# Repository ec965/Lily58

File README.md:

# SMD Lily58
* ATMEGA32U4 and STM32F072 variants
* Full SMD MCU and components.
* Original parts kept true to original placement where ever possible.
* Reversible PCB to reduce costs.
* USB C port on the left side.
* MCP23017 IO expander to reduce cost over two MCUs.

# Lily58
Lily58 is 6*4+4keys column-staggered split keyboard.

## [Document Site Here](https://kata0510.github.io/Lily58-Document/)

# Type

- Lily58 Pro
  - [PCB Data](https://github.com/kata0510/Lily58/tree/master/Pro/PCB)
  - [BuildGuide JP](https://kata0510.github.io/Lily58-Document/Lily58_Pro.html)
  - [BuildGuide EN](https://kata0510.github.io/Lily58-Document/Lily58_Pro_BG_ENG.html)
  - [Shop(Yushakobo)](https://yushakobo.jp/shop/lily58-pro/)
- Lily58 Lite Rev2
  - [BuildGuide(YouTube)](https://www.youtube.com/watch?v=t6HLQvqlsVM)
  - [BuildInfo](https://kata0510.github.io/Lily58-Document/Lily58_Lite_Rev2.html)
  - [Shop(BOOTH)](https://booth.pm/ja/items/1963895)
  - [Shop(Yushakobo)](https://yushakobo.jp/shop/consign_lily58-lite-rev2/)
- Lily58(Old)
  - [PCB Data](https://github.com/kata0510/Lily58/tree/master/pcb)
  - [BuildGuide](https://kata0510.github.io/Lily58-Document/Lily58_BG.html)
- Lily58 Lite Rev1(Old)
  - [PCB Data](https://github.com/kata0510/Lily58/tree/master/pcb)
  - [BuildGuide](https://kata0510.github.io/Lily58-Document/Lily58_Lite_BG.html)

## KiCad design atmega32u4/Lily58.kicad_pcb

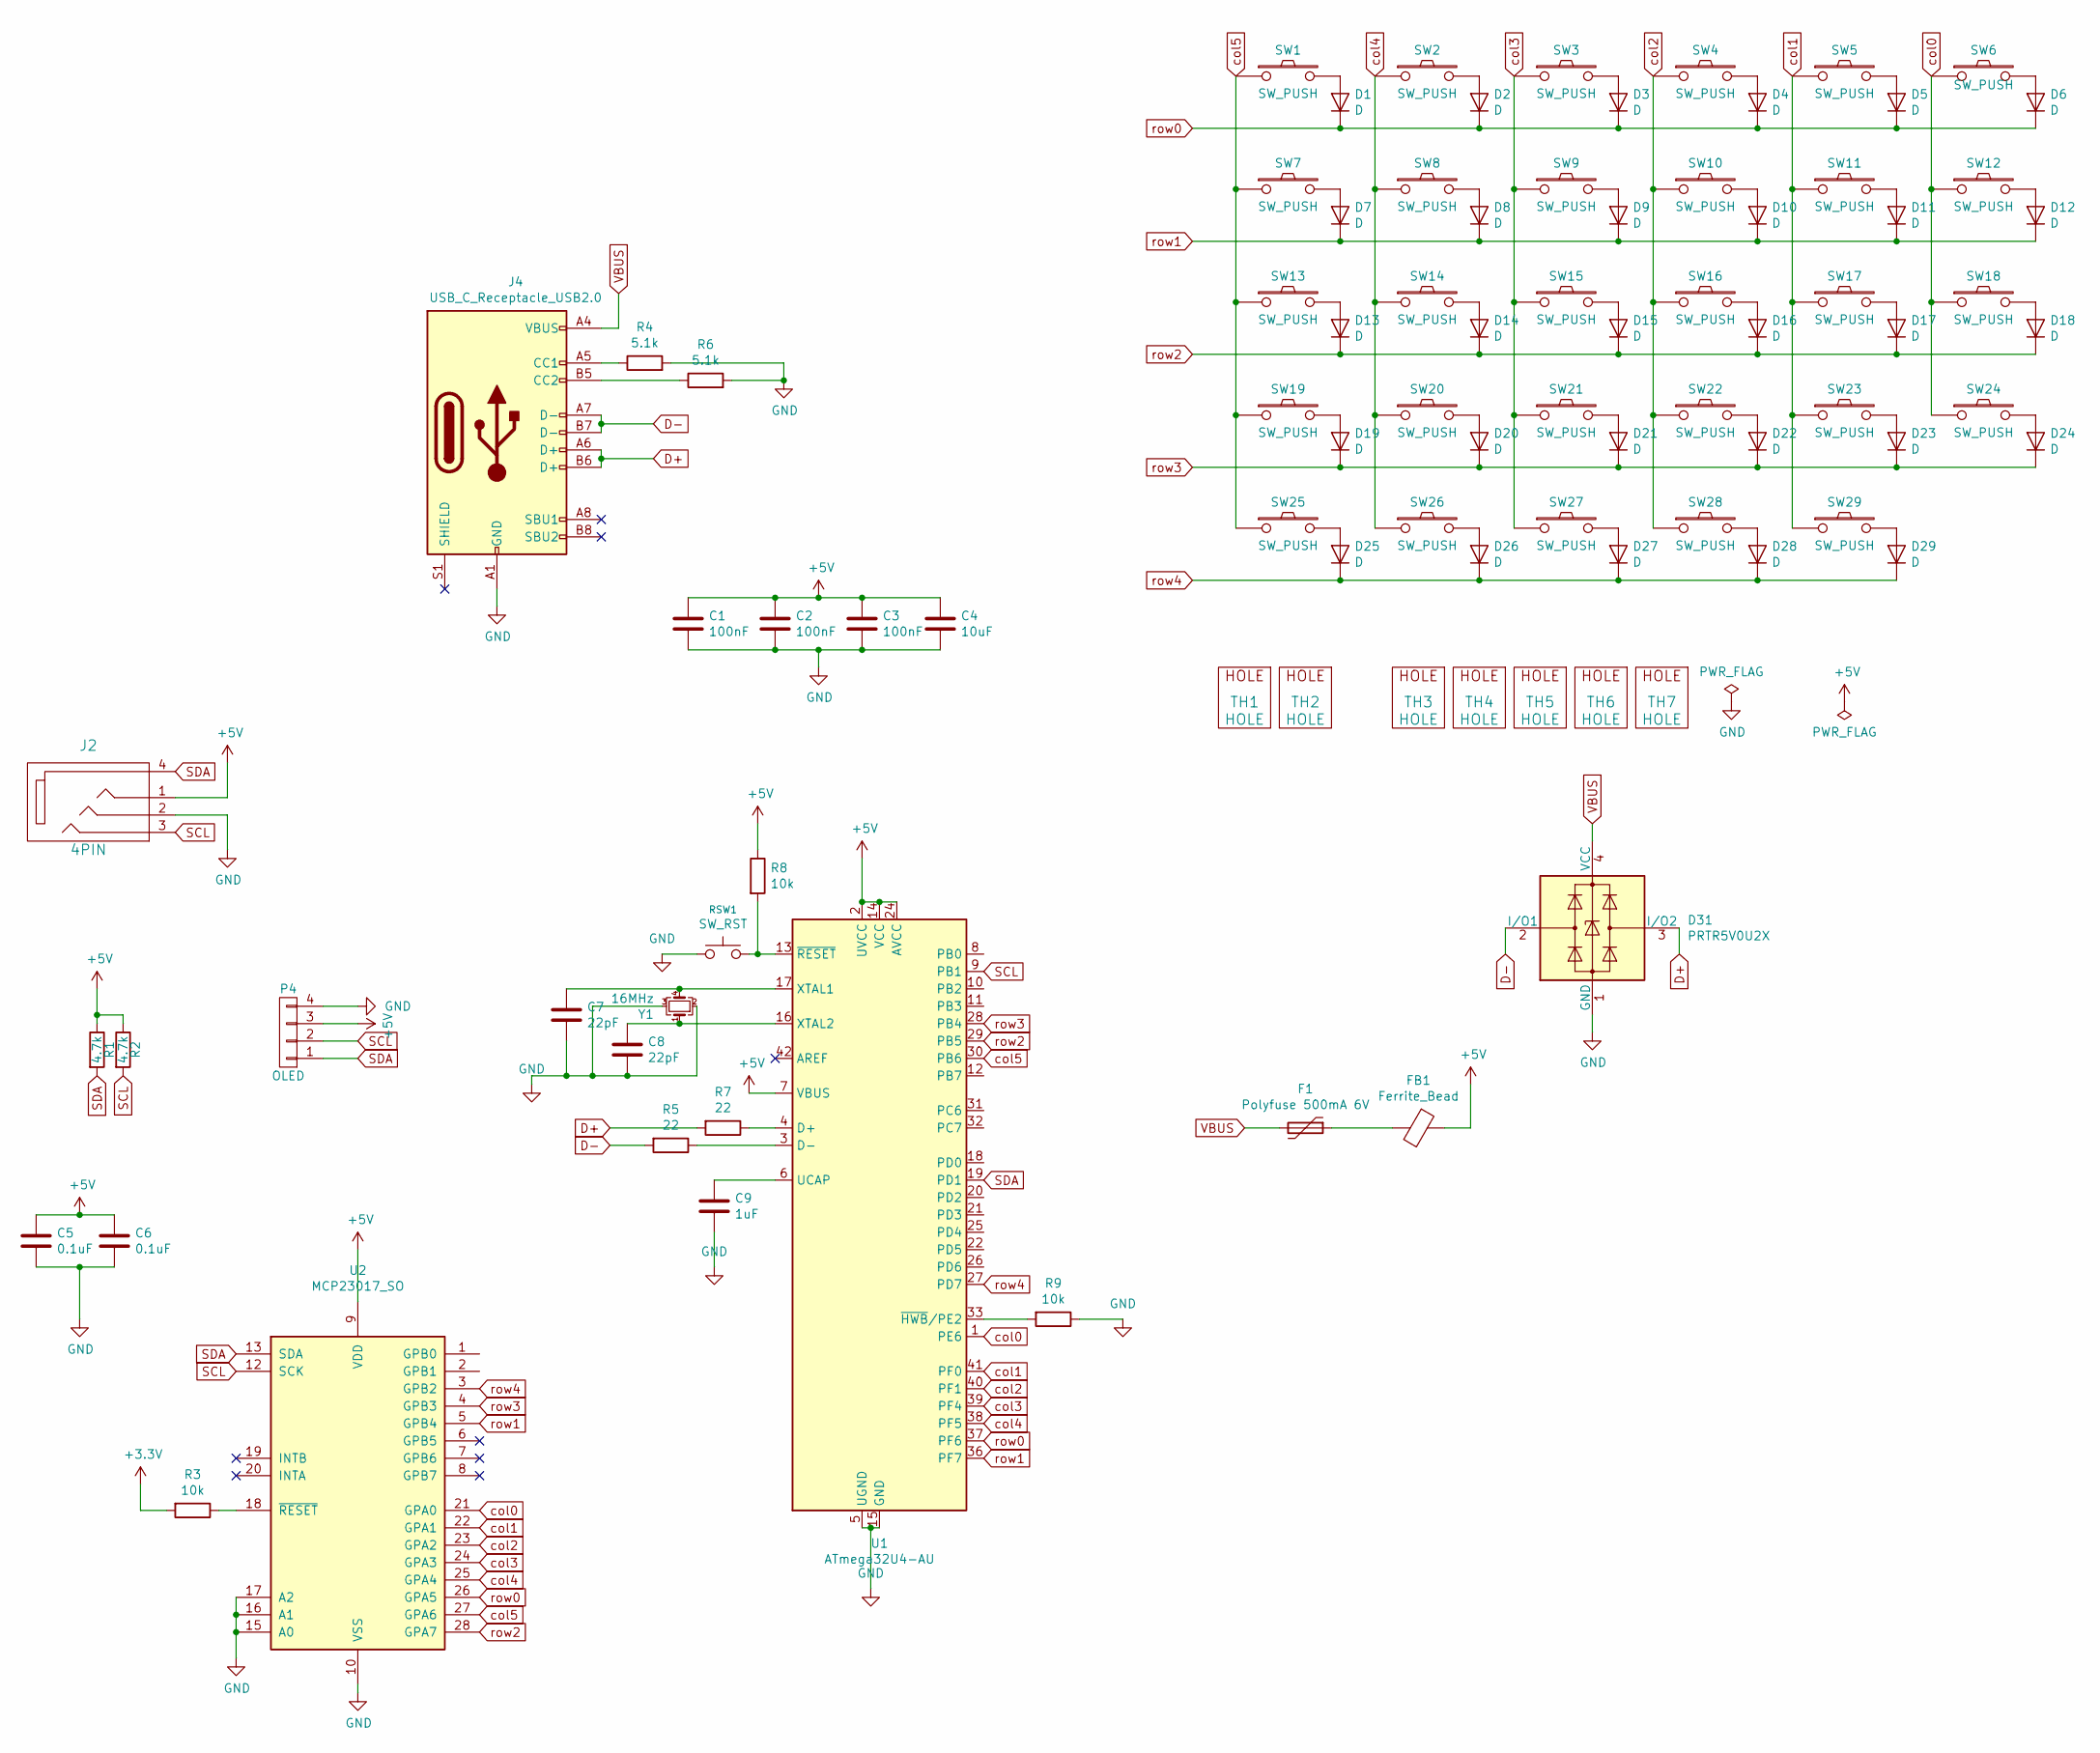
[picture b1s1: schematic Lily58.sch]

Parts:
C1, C2, C3: 100nF; C_0805_2012Metric
C4: 10uF; C_0805_2012Metric
C5, C6: 0.1uF; C_0805_2012Metric
C7, C8: 22pF; C_0805_2012Metric
C9: 1uF; C_0805_2012Metric
D1, D2, D3, D4, D5, D6, D7, D8, D9, D10, D11, D12, D13, D14, D15, D16, D17, D18, D19, D20, D21, D22, D23, D24, D25, D26, D27, D28, D29: D; Diode_TH_SOD123
D31: PRTR5V0U2X; SOT-143
F1: Polyfuse 500mA 6V; R_0805_2012Metric
FB1: Ferrite_Bead; L_0805_2012Metric
J2: 4PIN; MJ-4PP-9
J4: USB_C_Receptacle_USB2.0; USB_C_Receptacle_Palconn_UTC16-G
P4: OLED; MY_SIL-4
R1, R2: 4.7k; R_0805_2012Metric
R3, R8, R9: 10k; R_0805_2012Metric
R4, R6: 5.1k; R_0805_2012Metric
R5, R7: 22; R_0805_2012Metric
RSW1: SW_RST; TACT_SWITCH_TVBP06
SW1, SW2, SW3, SW4, SW5, SW6, SW7, SW8, SW9, SW10, SW11, SW12, SW13, SW14, SW15, SW16, SW17, SW18, SW19, SW20, SW21, SW22, SW23, SW24, SW25, SW27, SW28, SW29: SW_PUSH; MX_PG1350-Under_FLIP_HOLES_18mm
SW26: SW_PUSH; MX_PG1350-Under_FLIP_HOLES_27mm
TH1, TH2: HOLE; HOLE_M2
TH3, TH4, TH5, TH6, TH7: HOLE; HOLE_M2_TH
U1: ATmega32U4-AU; TQFP-44_10x10mm_P0.8mm
U2: MCP23017_SO; SOIC-28W_7.5x17.9mm_P1.27mm
Y1: 16MHz; Crystal_SMD_3225-4Pin_3.2x2.5mm

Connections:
D+: D31.3 (I/O2), J4.A6 (D+), J4.B6 (D+), R7.2
D-: D31.2 (I/O1), J4.A7 (D-), J4.B7 (D-), R5.2
GND: C1.2, C2.2, C3.2, C4.2, C5.2, C6.2, C7.2, C8.1, C9.2, D31.1 (GND), J2.2, J4.A1 (GND), J4.A12 (GND), J4.B1 (GND), J4.B12 (GND), P4.4, R4.2, R6.2, R9.1, RSW1.1, U1.5 (UGND), U1.15 (GND), U1.23 (GND), U1.35 (GND), U1.43 (GND), U2.10 (VSS), U2.15 (A0), U2.16 (A1), U2.17 (A2), Y1.2, Y1.3
unnamed: C7.1, U1.17 (XTAL1), Y1.4
unnamed: C8.2, U1.16 (XTAL2), Y1.1
unnamed: C9.1, U1.6 (UCAP)
unnamed: D1.2 (A), SW1.2
unnamed: D2.2 (A), SW2.2
unnamed: D3.2 (A), SW3.2
unnamed: D4.2 (A), SW4.2
unnamed: D5.2 (A), SW5.2
unnamed: D6.2 (A), SW6.2
unnamed: D7.2 (A), SW7.2
unnamed: D8.2 (A), SW8.2
unnamed: D9.2 (A), SW9.2
unnamed: D10.2 (A), SW10.2
unnamed: D11.2 (A), SW11.2
unnamed: D12.2 (A), SW12.2
unnamed: D13.2 (A), SW13.2
unnamed: D14.2 (A), SW14.2
unnamed: D15.2 (A), SW15.2
unnamed: D16.2 (A), SW16.2
unnamed: D17.2 (A), SW17.2
unnamed: D18.2 (A), SW18.2
unnamed: D19.2 (A), SW19.2
unnamed: D20.2 (A), SW20.2
unnamed: D21.2 (A), SW21.2
unnamed: D22.2 (A), SW22.2
unnamed: D23.2 (A), SW23.2
unnamed: D24.2 (A), SW24.2
unnamed: D25.2 (A), SW25.2
unnamed: D26.2 (A), SW26.2
unnamed: D27.2 (A), SW27.2
unnamed: D28.2 (A), SW28.2
unnamed: D29.2 (A), SW29.2
unnamed: F1.1, FB1.2
unnamed: J4.A5 (CC1), R4.1
unnamed: J4.B5 (CC2), R6.1
unnamed: R3.1, U2.18 (~RESET~)
unnamed: R5.1, U1.3 (D-)
unnamed: R7.1, U1.4 (D+)
unnamed: R8.2, RSW1.2, U1.13 (~RESET)
unnamed: R9.2, U1.33 (~HWB~/PE2)
SCL: J2.3, P4.2, R2.2, U1.9 (PB1), U2.12 (SCK)
SDA: J2.4, P4.1, R1.2, U1.19 (PD1), U2.13 (SDA)
VBUS: D31.4 (VCC), F1.2, J4.A4 (VBUS), J4.A9 (VBUS), J4.B4 (VBUS), J4.B9 (VBUS)
col0: SW6.1, SW12.1, SW18.1, SW24.1, U1.1 (PE6), U2.21 (GPA0)
col1: SW5.1, SW11.1, SW17.1, SW23.1, SW29.1, U1.41 (PF0), U2.22 (GPA1)
col2: SW4.1, SW10.1, SW16.1, SW22.1, SW28.1, U1.40 (PF1), U2.23 (GPA2)
col3: SW3.1, SW9.1, SW15.1, SW21.1, SW27.1, U1.39 (PF4), U2.24 (GPA3)
col4: SW2.1, SW8.1, SW14.1, SW20.1, SW26.1, U1.38 (PF5), U2.25 (GPA4)
col5: SW1.1, SW7.1, SW13.1, SW19.1, SW25.1, U1.30 (PB6), U2.27 (GPA6)
row0: D1.1 (K), D2.1 (K), D3.1 (K), D4.1 (K), D5.1 (K), D6.1 (K), U1.37 (PF6), U2.26 (GPA5)
row1: D7.1 (K), D8.1 (K), D9.1 (K), D10.1 (K), D11.1 (K), D12.1 (K), U1.36 (PF7), U2.5 (GPB4)
row2: D13.1 (K), D14.1 (K), D15.1 (K), D16.1 (K), D17.1 (K), D18.1 (K), U1.29 (PB5), U2.28 (GPA7)
row3: D19.1 (K), D20.1 (K), D21.1 (K), D22.1 (K), D23.1 (K), D24.1 (K), U1.28 (PB4), U2.4 (GPB3)
row4: D25.1 (K), D26.1 (K), D27.1 (K), D28.1 (K), D29.1 (K), U1.27 (PD7), U2.3 (GPB2)

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
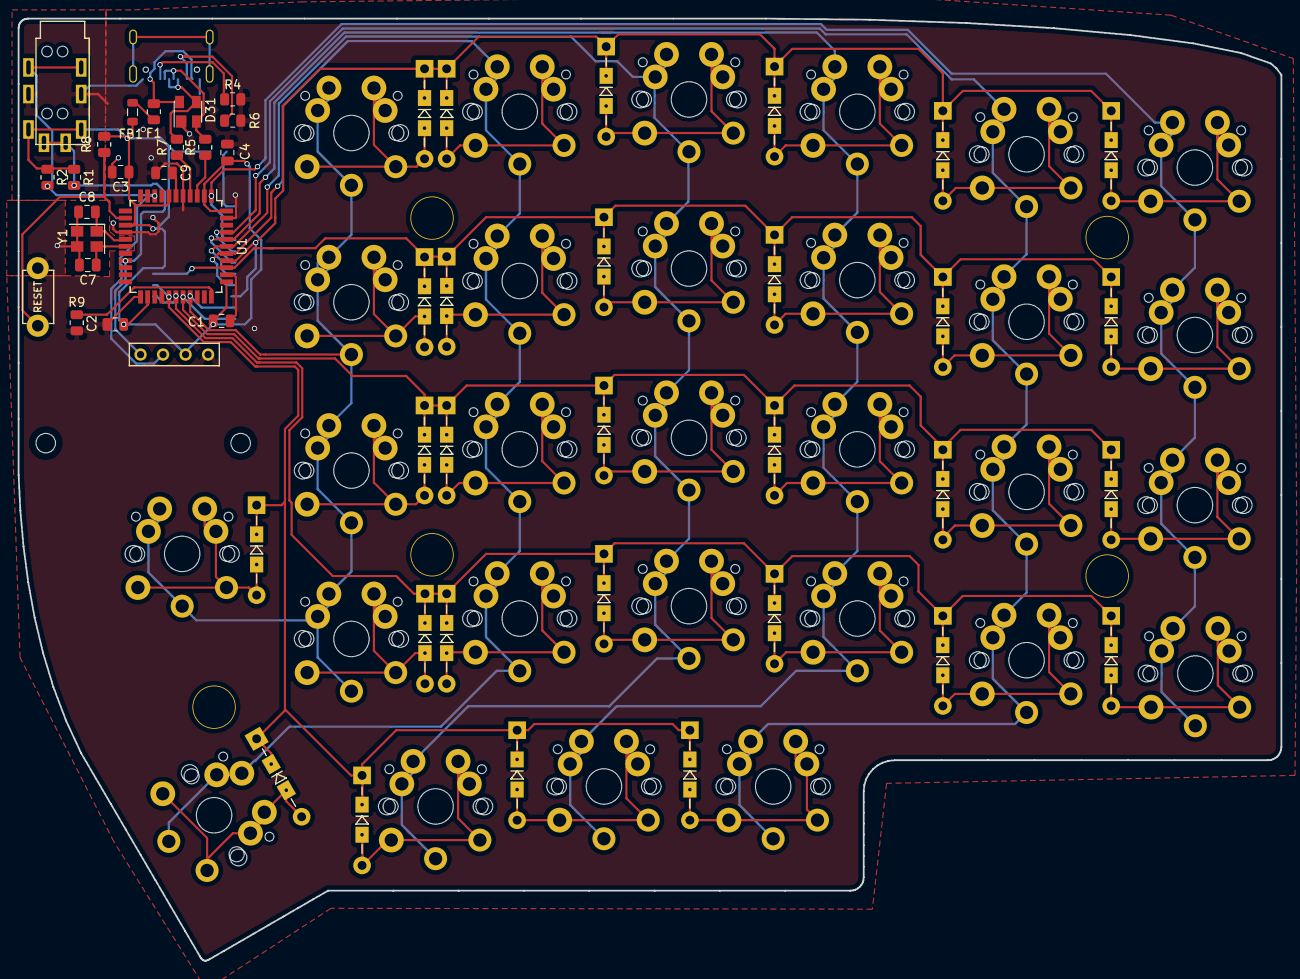
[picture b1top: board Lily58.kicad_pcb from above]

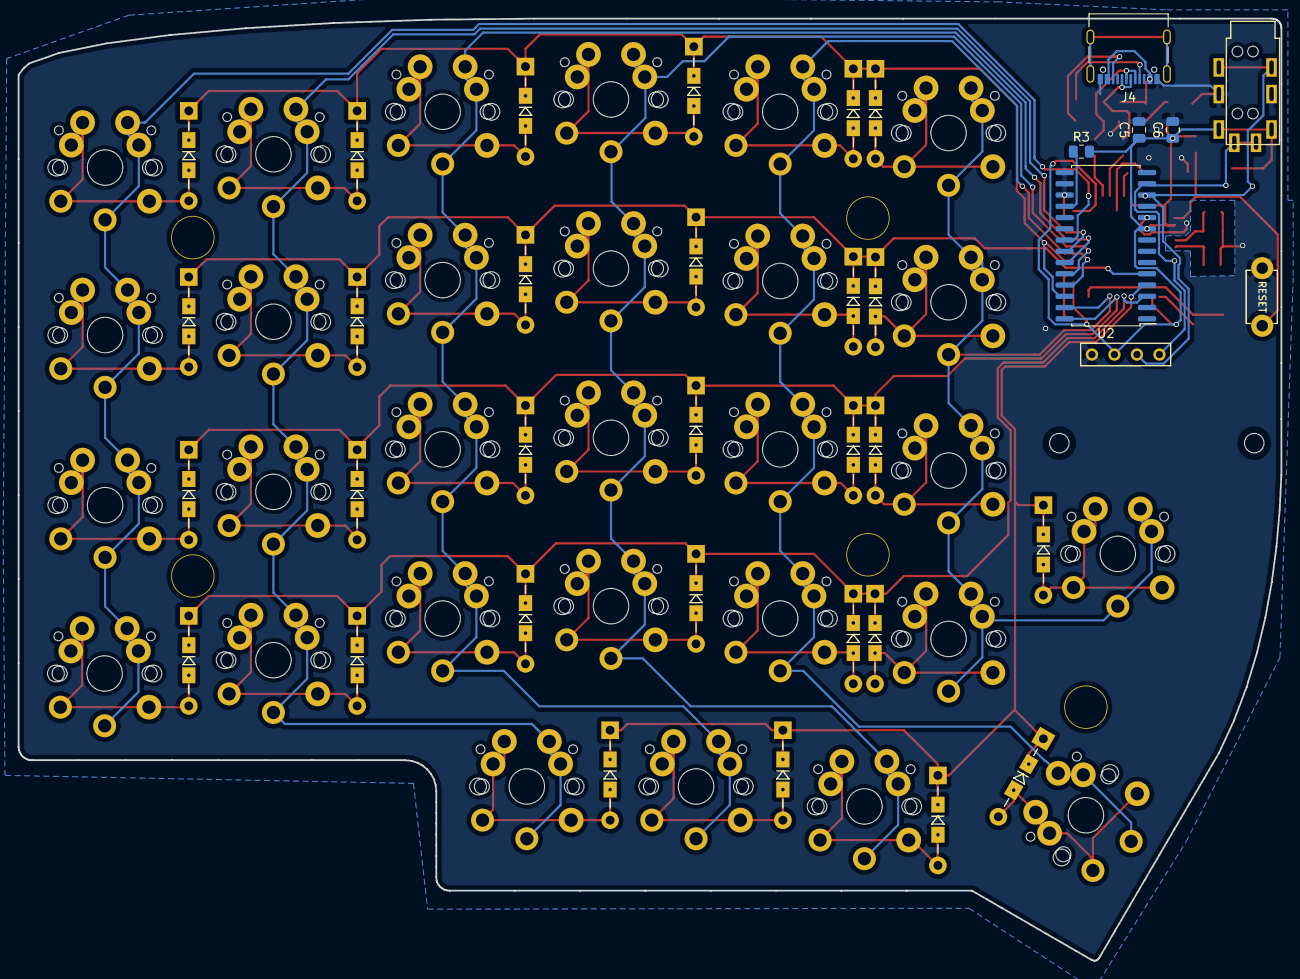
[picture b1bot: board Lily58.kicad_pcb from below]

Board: 2 copper layers, 142.5 x 106.3 mm, 93 parts (5 on the bottom side), 58 nets.

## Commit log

2021-03-24 setting up schematic and pcb
2021-03-24 finishing pcb
2021-03-24 README notes
2021-03-25 adding atmega version
2021-03-25 removing ldo on atmega32u4
